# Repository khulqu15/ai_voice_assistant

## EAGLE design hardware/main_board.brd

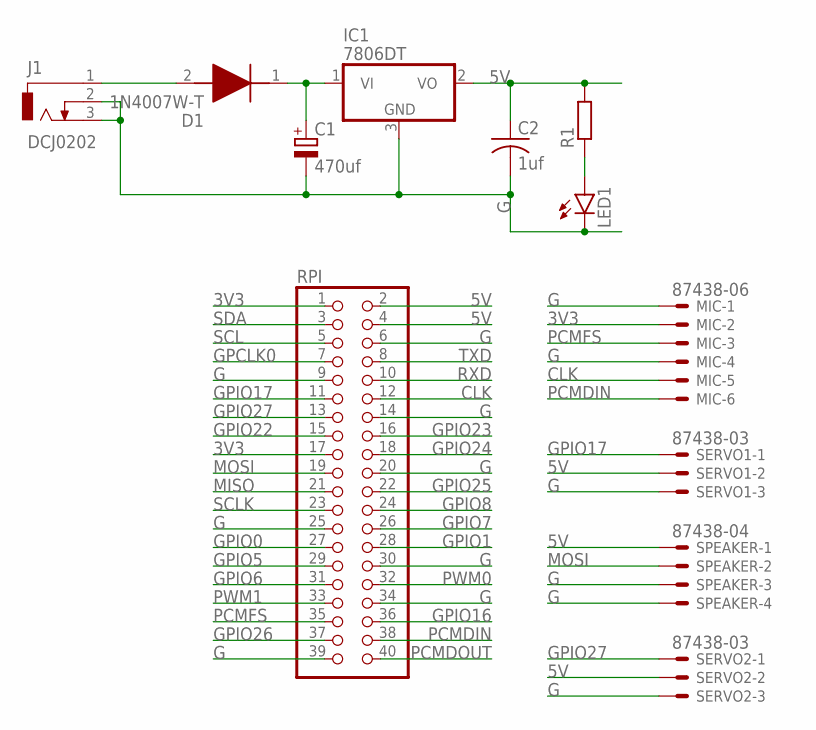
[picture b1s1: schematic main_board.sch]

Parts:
C1: 470uf; PANASONIC_D
C2: 1uf; C0805
D1: 1N4007W-T; SODFL3818X130N
IC1: 7806DT; TO252
J1: DCJ0202
LED1: LEDCHIP-LED0805; CHIP-LED0805
MIC: 87438-06
R1: R-EU_R0603; R0603
RPI: PINHD-2X20; 2X20
SERVO1, SERVO2: 87438-03
SPEAKER: 87438-04

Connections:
3V3: MIC.2, RPI.1, RPI.17
5V: C2.1, IC1.2 (VO), R1.2, RPI.2, RPI.4, SERVO1.2, SERVO2.2, SPEAKER.1
CLK: MIC.5, RPI.12
G: C1.-, C2.2, IC1.3 (GND), J1.2, J1.3, LED1.C, MIC.1, MIC.4, RPI.6, RPI.9, RPI.14, RPI.20, RPI.25, RPI.30, RPI.34, RPI.39, SERVO1.3, SERVO2.3, SPEAKER.3, SPEAKER.4
GPCLK0: RPI.7
GPIO0: RPI.27
GPIO1: RPI.28
GPIO5: RPI.29
GPIO6: RPI.31
GPIO7: RPI.26
GPIO8: RPI.24
GPIO16: RPI.36
GPIO17: RPI.11, SERVO1.1
GPIO22: RPI.15
GPIO23: RPI.16
GPIO24: RPI.18
GPIO25: RPI.22
GPIO26: RPI.37
GPIO27: RPI.13, SERVO2.1
MISO: RPI.21
MOSI: RPI.19, SPEAKER.2
unnamed: C1.+, D1.1 (K), IC1.1 (VI)
unnamed: LED1.A, R1.1
unnamed: D1.2 (A), J1.1
PCMDIN: MIC.6, RPI.38
PCMDOUT: RPI.40
PCMFS: MIC.3, RPI.35
PWM0: RPI.32
PWM1: RPI.33
RXD: RPI.10
SCL: RPI.5
SCLK: RPI.23
SDA: RPI.3
TXD: RPI.8

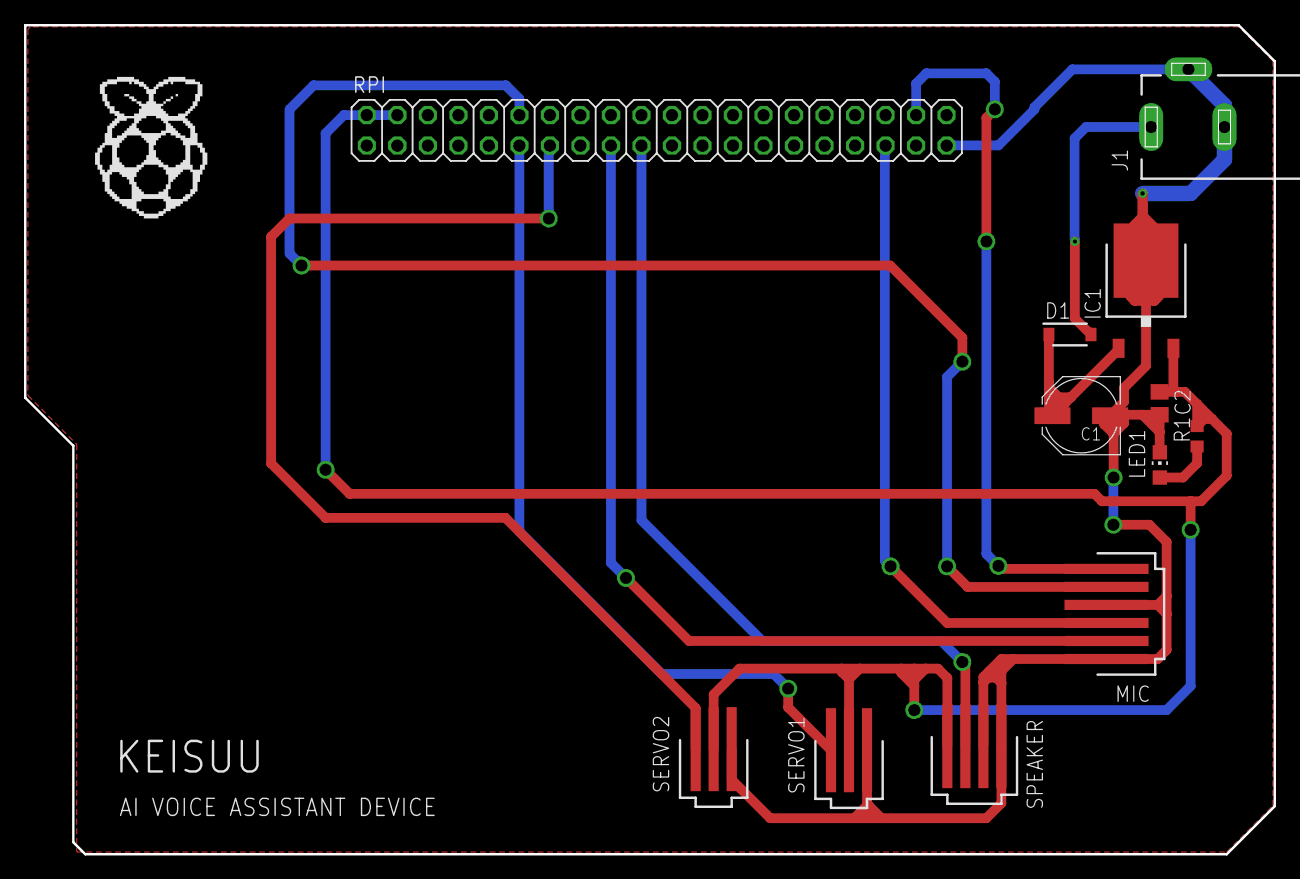
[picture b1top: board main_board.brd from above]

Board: 2 copper layers, 104.0 x 69.0 mm, 12 parts (0 on the bottom side), 12 nets.

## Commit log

2024-01-31 add 4 commands for hello, good morning, play a song, and weather information
